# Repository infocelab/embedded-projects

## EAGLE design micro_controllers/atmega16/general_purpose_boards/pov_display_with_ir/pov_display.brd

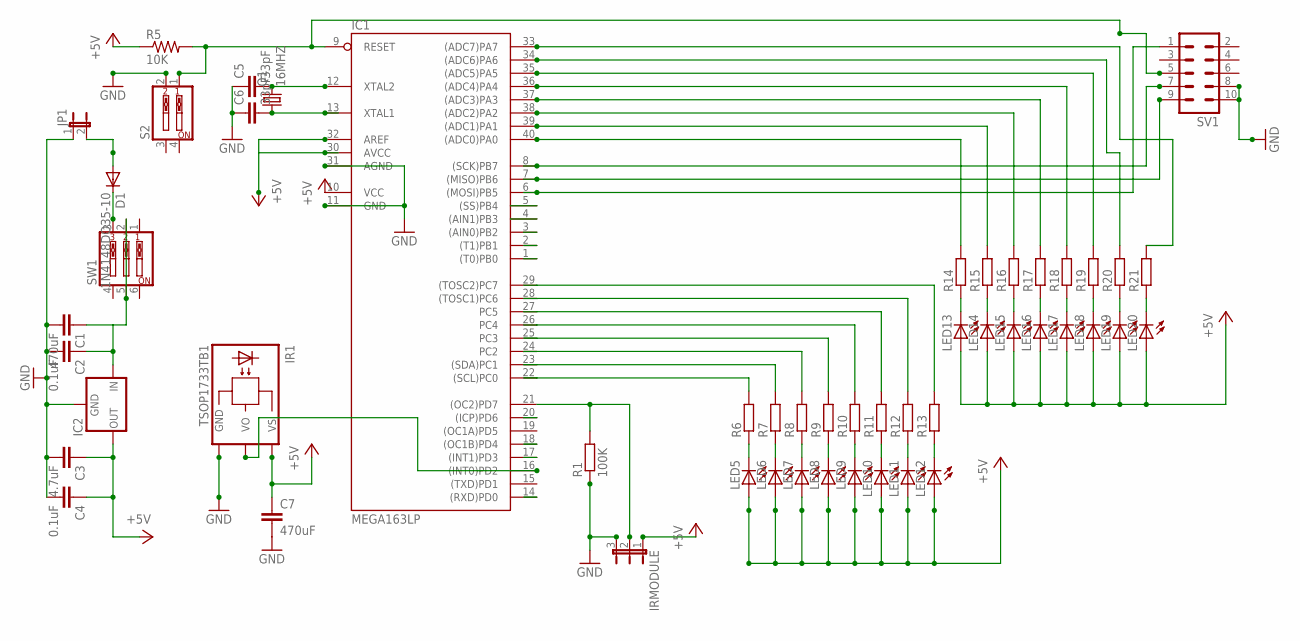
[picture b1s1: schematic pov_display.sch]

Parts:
C1, C7: 470uF; C2.5-4
C2, C4: 0.1uF; C2.5-4
C3: 4.7uF; C2.5-4
C5, C6: 33pF; C2.5-4
D1: 1N4148DO35-10; DO35-10
IC1: MEGA163LP; DIL40
IC2: 78XXS
IR1: TSOP1733TB1; TSOP17_TB1
IRMODULE: JP2W
JP1: JP1E; JP1
LED5, LED6, LED7, LED8, LED9, LED10, LED11, LED12, LED13, LED14, LED15, LED16, LED17, LED18, LED19, LED20: LED_ELD260; LED_LD260
Q1: 16MHZ; HC49U-V
R1: 100K; 0207/7
R5: 10K; 0204/7
R6, R7, R8, R9, R10, R11, R12, R13, R14, R15, R16, R17, R18, R19, R20, R21: R-EU_0207/7; 0207/7
S2: SW_DIP-2; EDG-02
SV1: MA05-2
SW1: SW_DIP-3; EDG-03

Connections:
+5V: C3.1, C4.1, C7.1, IC1.10 (VCC), IC1.30 (AVCC), IC1.32 (AREF), IC2.OUT, IR1.VS, IRMODULE.1, LED5.A, LED6.A, LED7.A, LED8.A, LED9.A, LED10.A, LED11.A, LED12.A, LED13.A, LED14.A, LED15.A, LED16.A, LED17.A, LED18.A, LED19.A, LED20.A, R5.1
GND: C1.2, C2.2, C3.2, C4.2, C5.1, C6.1, C7.2, IC1.11 (GND), IC1.31 (AGND), IC2.GND, IR1.GND, IRMODULE.3, JP1.1, R1.1, S2.2, SV1.8, SV1.10
unnamed: D1.A, JP1.2
unnamed: LED12.K (C), R13.1
unnamed: C5.2, IC1.12 (XTAL2), Q1.2
unnamed: C6.2, IC1.13 (XTAL1), Q1.1
unnamed: IC1.9 (RESET), R5.2, S2.1, SV1.5
unnamed: IC1.22 ((SCL)PC0), R6.2
unnamed: D1.C, SW1.3
unnamed: C1.1, C2.1, IC2.IN, SW1.2, SW1.5
unnamed: IC1.21 ((OC2)PD7), IRMODULE.2, R1.2
unnamed: IC1.28 ((TOSC1)PC6), R12.2
unnamed: LED10.K (C), R11.1
unnamed: IC1.26 (PC4), R10.2
unnamed: LED9.K (C), R10.1
unnamed: IC1.25 (PC3), R9.2
unnamed: LED8.K (C), R9.1
unnamed: LED7.K (C), R8.1
unnamed: IC1.6 ((MOSI)PB5), SV1.1
unnamed: IC1.7 ((MISO)PB6), SV1.9
unnamed: IC1.8 ((SCK)PB7), SV1.7
unnamed: IC1.23 ((SDA)PC1), R7.2
unnamed: IC1.33 ((ADC7)PA7), R21.2
unnamed: IC1.34 ((ADC6)PA6), R20.2
unnamed: IC1.35 ((ADC5)PA5), R19.2
unnamed: IC1.36 ((ADC4)PA4), R18.2
unnamed: IC1.37 ((ADC3)PA3), R17.2
unnamed: IC1.38 ((ADC2)PA2), R16.2
unnamed: IC1.39 ((ADC1)PA1), R15.2
unnamed: IC1.40 ((ADC0)PA0), R14.2
unnamed: IC1.24 (PC2), R8.2
unnamed: IC1.27 (PC5), R11.2
unnamed: IC1.29 ((TOSC2)PC7), R13.2
unnamed: LED6.K (C), R7.1
unnamed: LED20.K (C), R21.1
unnamed: LED19.K (C), R20.1
unnamed: LED18.K (C), R19.1
unnamed: LED17.K (C), R18.1
unnamed: LED15.K (C), R16.1
unnamed: LED13.K (C), R14.1
unnamed: LED16.K (C), R17.1
unnamed: LED14.K (C), R15.1
unnamed: LED5.K (C), R6.1
unnamed: LED11.K (C), R12.1
unnamed: IC1.16 ((INT0)PD2), IR1.VO

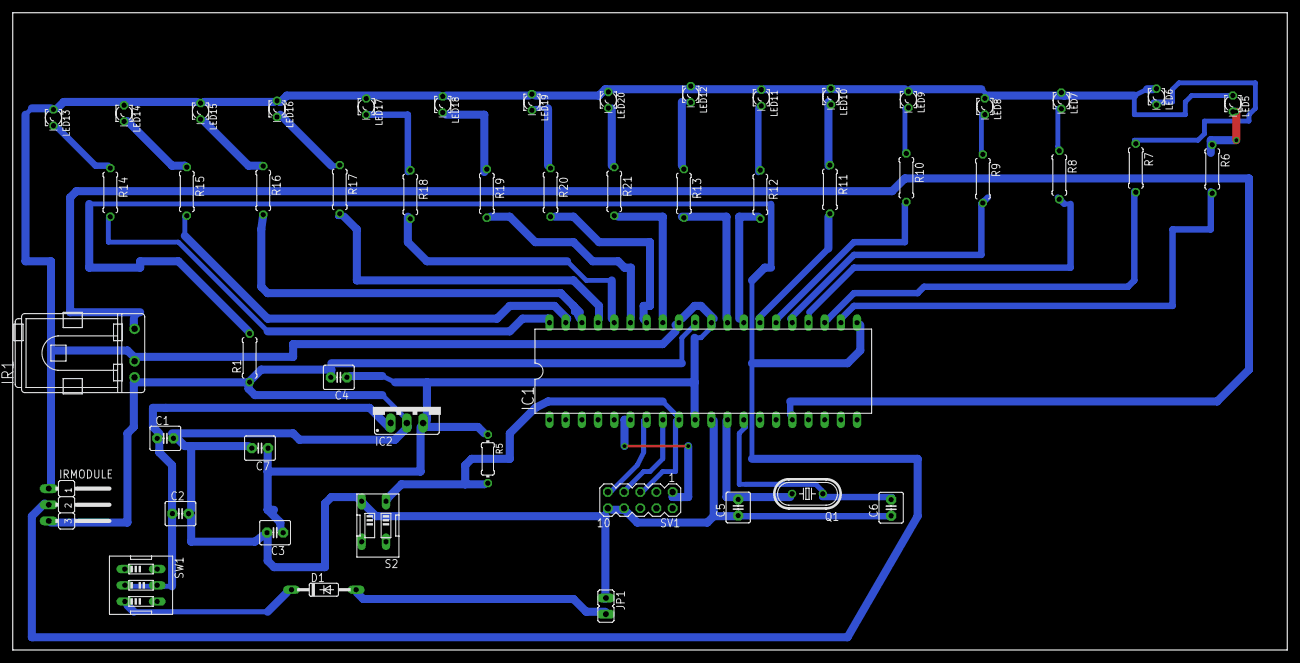
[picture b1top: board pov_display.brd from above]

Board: 2 copper layers, 200.0 x 100.0 mm, 51 parts (0 on the bottom side), 45 nets.

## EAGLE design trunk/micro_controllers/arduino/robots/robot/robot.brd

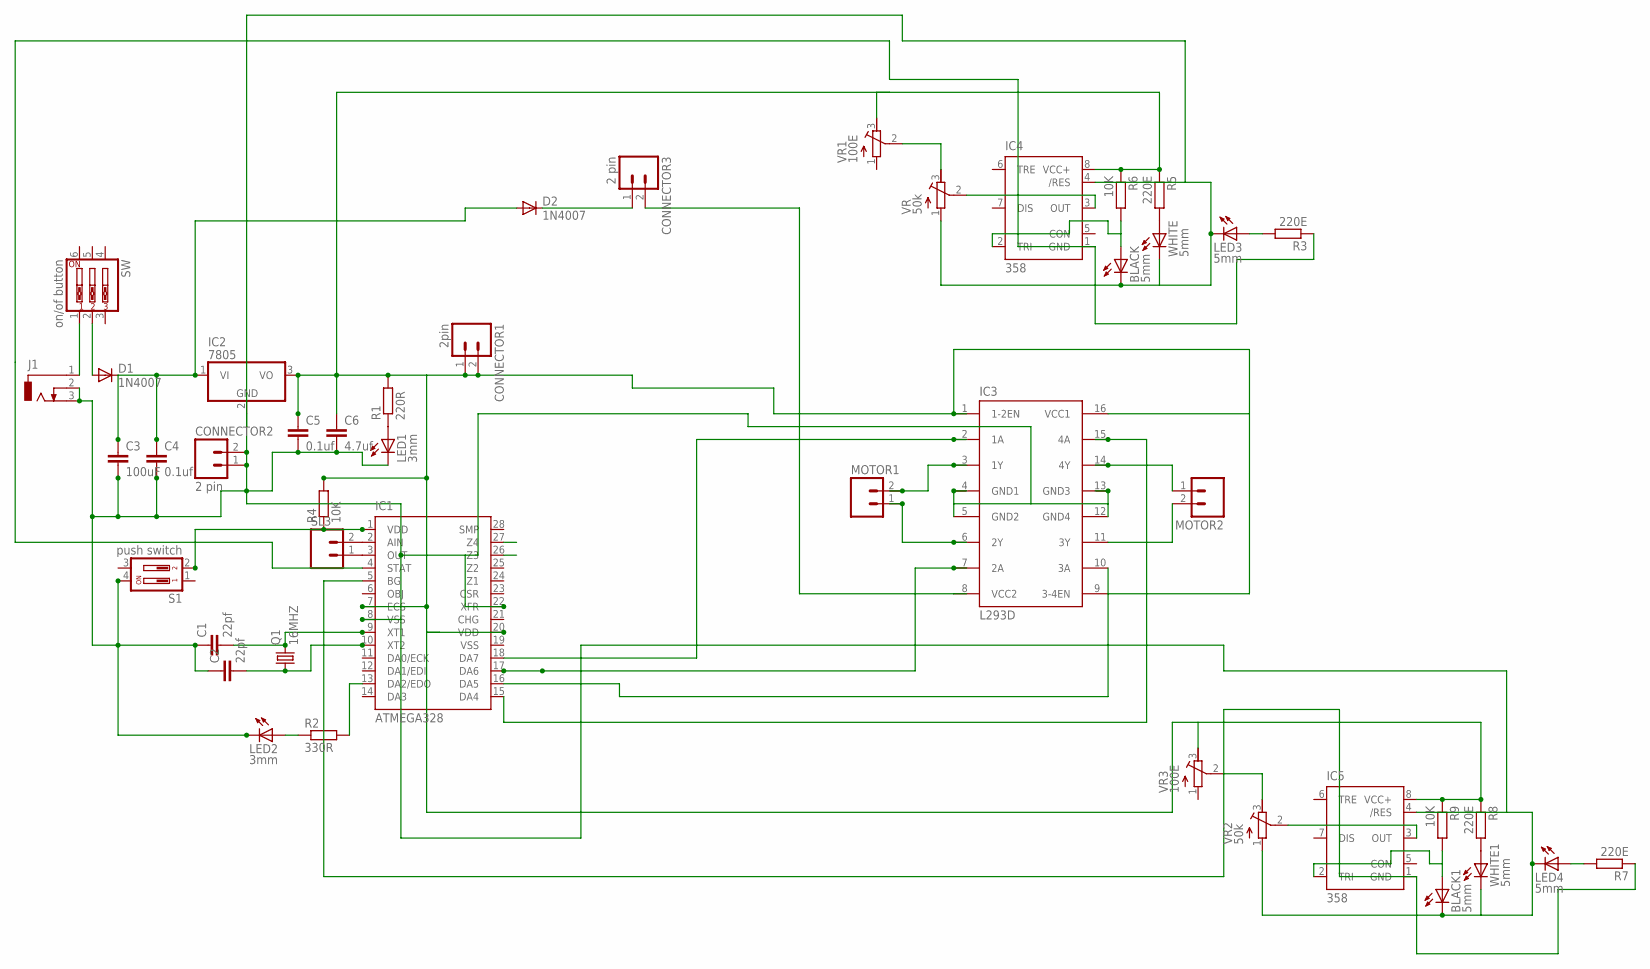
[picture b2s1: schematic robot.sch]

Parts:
BLACK, BLACK1: 5mm; LED5MM
C1, C2: 22pf; C2.5-2
C3: 100uF; C2.5-2
C4, C5: 0.1uf; C2.5-2
C6: 4.7uf; C2.5-2
CONNECTOR1: 2pin; 02P
CONNECTOR2, CONNECTOR3: 2 pin; 02P
D1, D2: 1N4007; DO41-10
IC1: ATMEGA328; DIL28-3
IC2: 7805; TO220V
IC3: L293D; DIL16
IC4, IC5: 358; DIL-08
J1: DCJ0303
LED1, LED2: 3mm; LED3MM
LED3, LED4: 5mm; LED5MM
MOTOR1, MOTOR2: M02; 02P
Q1: 16MHZ; HC49/S
R1: 220R; 0207/10
R2: 330R; 0207/10
R3, R5, R7, R8: 220E; 0204/7
R4: 10K; 0207/10
R6, R9: 10K; 0204/7
S1: push switch; DP-02
SL3: M02; 02P
SW: on/of button; EDG-03
VR, VR2: 50k; RTRIM64P
VR1, VR3: 100E; RTRIM64P
WHITE, WHITE1: 5mm; LED5MM

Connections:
unnamed: C1.2, IC1.9 (XT1), Q1.2
unnamed: C2.2, IC1.10 (XT2), Q1.1
unnamed: J1.1, SW.1
unnamed: CONNECTOR3.2, IC3.8 (VCC2)
unnamed: C3.1, C4.1, D1.C, D2.A, IC2.1 (VI)
unnamed: LED1.A, R1.1
unnamed: IC1.17 (DA6), IC3.7 (2A)
unnamed: IC1.3 (OUT), SL3.1
unnamed: IC1.2 (AIN), SL3.2
unnamed: CONNECTOR3.1, D2.C
unnamed: IC1.18 (DA7), IC3.2 (1A)
unnamed: IC1.15 (DA4), IC3.15 (4A)
unnamed: IC1.13 (DA2/EDO), R2.2
unnamed: D1.A, SW.2
unnamed: IC1.4 (STAT), IC4.1 (GND), R3.1
unnamed: IC1.16 (DA5), IC3.10 (3A)
unnamed: R5.2, WHITE.A
unnamed: BLACK.A, IC4.2 (TRI), R6.2
unnamed: IC4.3 (OUT), VR.2 (S)
unnamed: IC3.14 (4Y), MOTOR2.1
unnamed: VR.3 (A), VR1.2 (S)
unnamed: IC3.11 (3Y), MOTOR2.2
unnamed: LED3.A, R3.2
unnamed: IC1.1 (VDD), R4.1, S1.2
unnamed: LED2.A, R2.1
unnamed: C5.1, C6.1, CONNECTOR1.1, CONNECTOR1.2, IC1.7 (ECS), IC1.20 (VDD), IC2.3 (VO), IC3.1 (1-2EN), IC3.9 (3-4EN), IC3.16 (VCC1), IC4.8 (VCC+), IC5.8 (VCC+), R1.2, R4.2, R5.1, R6.1, R8.1, R9.1, VR1.3 (A), VR3.3 (A)
unnamed: IC3.6 (2Y), MOTOR1.1
unnamed: IC3.3 (1Y), MOTOR1.2
unnamed: IC1.5 (BG), IC5.1 (GND), R7.1
unnamed: R8.2, WHITE1.A
unnamed: BLACK1.A, IC5.2 (TRI), R9.2
unnamed: IC5.3 (OUT), VR2.2 (S)
unnamed: VR2.3 (A), VR3.2 (S)
unnamed: BLACK.K (C), BLACK1.K (C), C1.1, C2.1, C3.2, C4.2, C5.2, C6.2, CONNECTOR2.1, CONNECTOR2.2, IC1.8 (VSS), IC1.22 (XFR), IC2.2 (GND), IC3.4 (GND1), IC3.5 (GND2), IC3.12 (GND4), IC3.13 (GND3), IC4.4 (/RES), IC5.4 (/RES), J1.2, J1.3, LED1.K (C), LED2.K (C), LED3.K (C), LED4.K (C), S1.4, VR.1 (E), VR2.1 (E), WHITE.K (C), WHITE1.K (C)
unnamed: LED4.A, R7.2

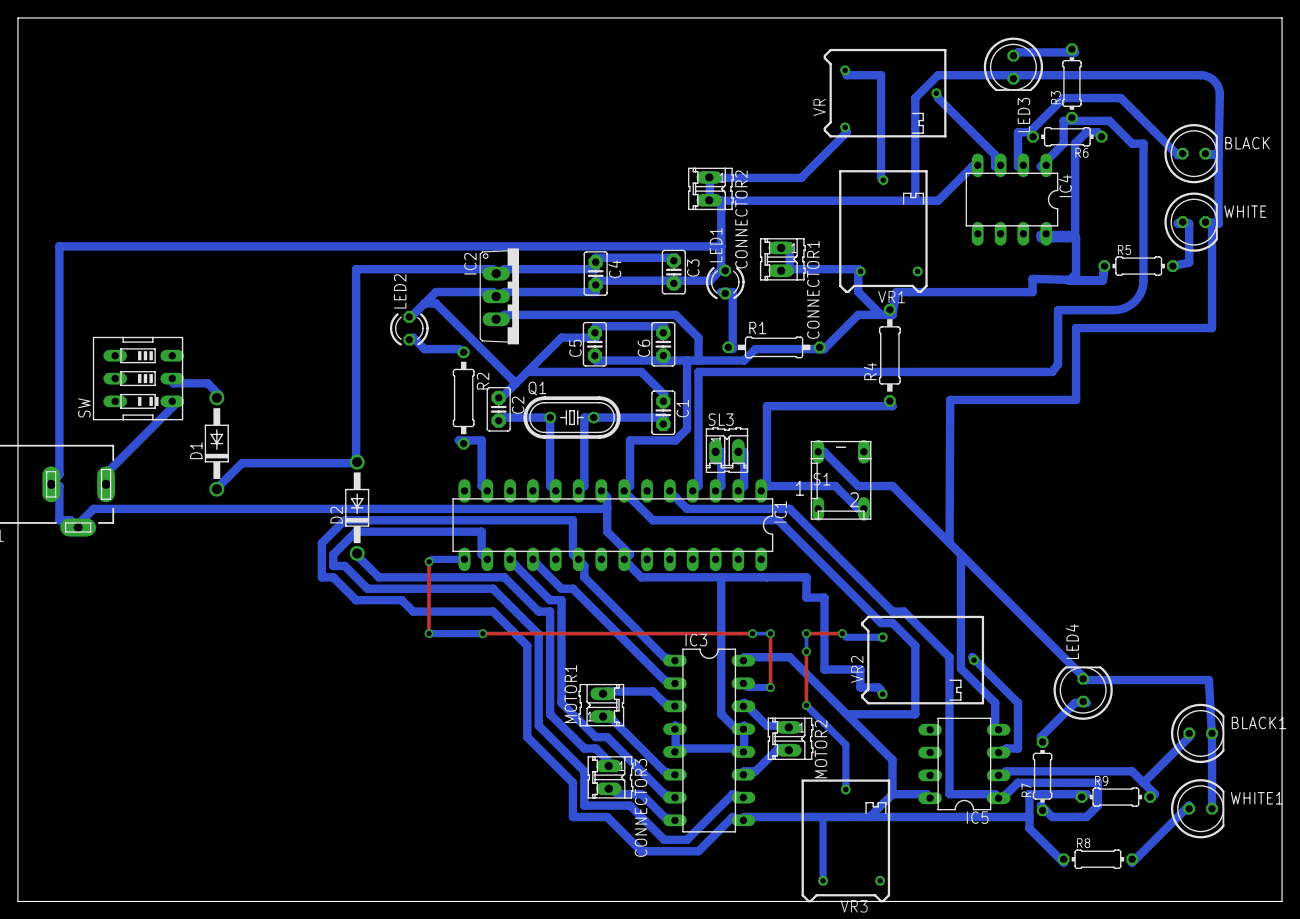
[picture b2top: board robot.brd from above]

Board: 2 copper layers, 140.7 x 98.3 mm, 44 parts (0 on the bottom side), 35 nets.

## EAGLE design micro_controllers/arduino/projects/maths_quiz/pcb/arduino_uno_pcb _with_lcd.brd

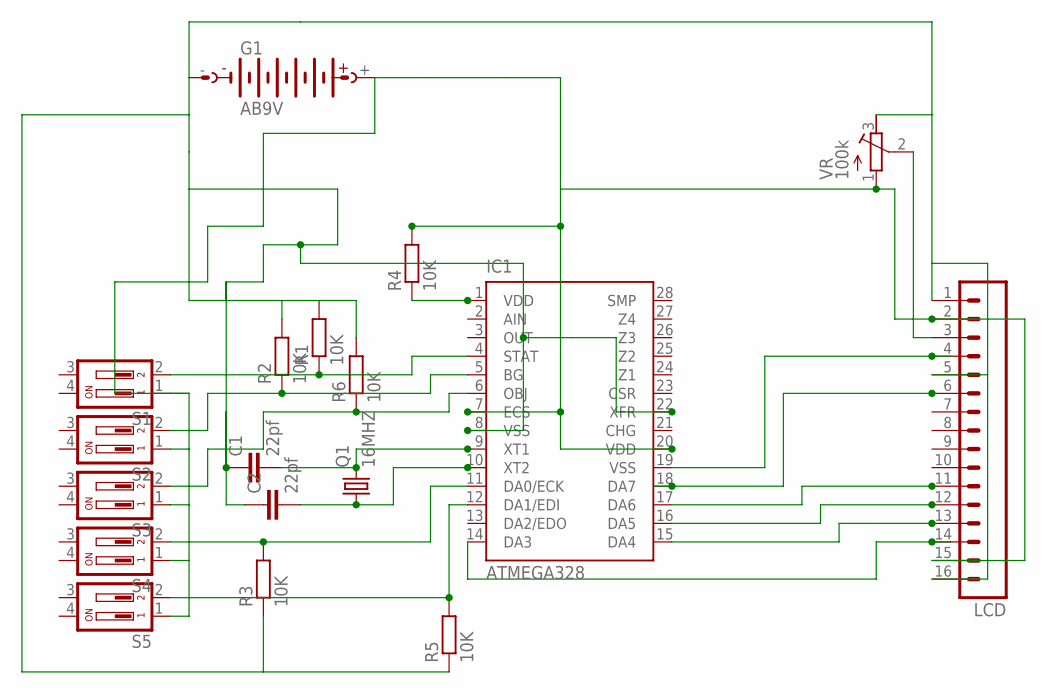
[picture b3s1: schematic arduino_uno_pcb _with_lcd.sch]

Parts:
C1, C2: 22pf; C2.5-2
G1: AB9V
IC1: ATMEGA328; DIL28-3
LCD: M16; 16P
Q1: 16MHZ; HC49/S
R1, R2, R3, R4, R5, R6: 10K; 0207/10
S1: DP02; DP-02
S2, S3, S4, S5: DP02; DP-02; MPN MCDP02
VR: 100k; RTRIM64P

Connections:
unnamed: C1.2, IC1.9 (XT1), Q1.2
unnamed: C2.2, IC1.10 (XT2), Q1.1
unnamed: G1.+, IC1.7 (ECS), IC1.20 (VDD), LCD.2, LCD.15, R4.2, S1.1, S2.1, S3.1, S4.1, S5.1, VR.1 (E)
unnamed: IC1.11 (DA0/ECK), R3.2, S4.2
unnamed: IC1.4 (STAT), R1.1, S1.2
unnamed: C1.1, C2.1, G1.-, IC1.8 (VSS), IC1.22 (XFR), LCD.1, LCD.5, LCD.16, R1.2, R2.2, R3.1, R5.1, R6.2, VR.3 (A)
unnamed: IC1.5 (BG), R2.1, S2.2
unnamed: IC1.6 (OBJ), R6.1, S3.2
unnamed: IC1.12 (DA1/EDI), R5.2, S5.2
unnamed: LCD.3, VR.2 (S)
unnamed: IC1.19 (VSS), LCD.4
unnamed: IC1.18 (DA7), LCD.6
unnamed: IC1.17 (DA6), LCD.11
unnamed: IC1.16 (DA5), LCD.12
unnamed: IC1.15 (DA4), LCD.13
unnamed: IC1.14 (DA3), LCD.14
unnamed: IC1.1 (VDD), R4.1

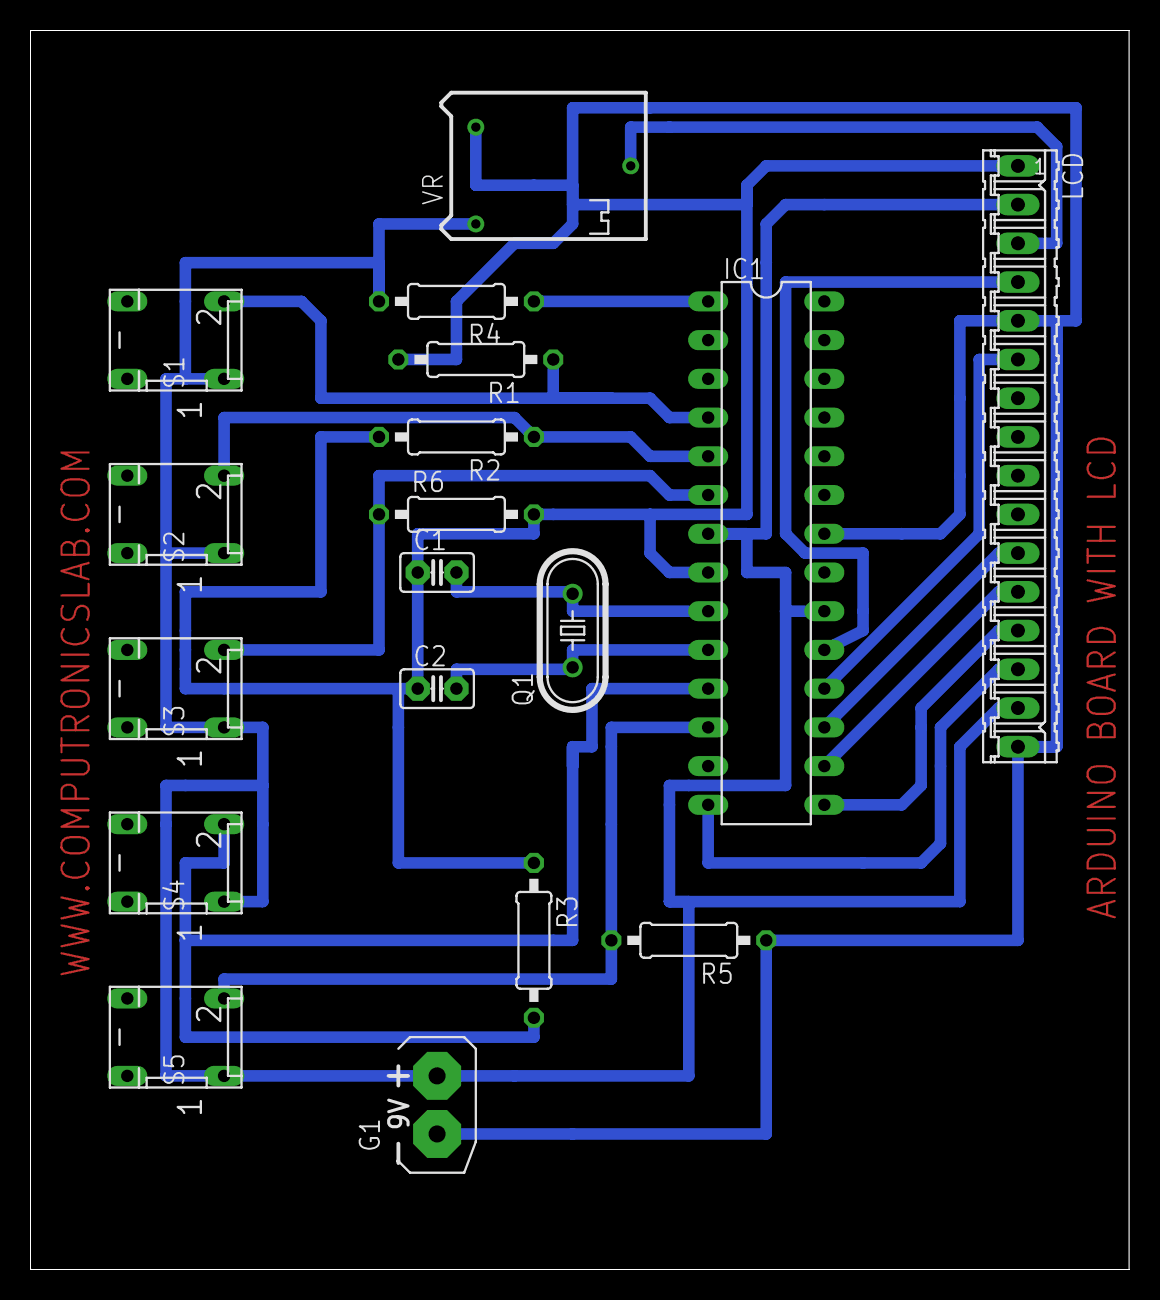
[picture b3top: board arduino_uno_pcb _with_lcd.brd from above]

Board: 2 copper layers, 72.1 x 81.3 mm, 18 parts (0 on the bottom side), 17 nets.

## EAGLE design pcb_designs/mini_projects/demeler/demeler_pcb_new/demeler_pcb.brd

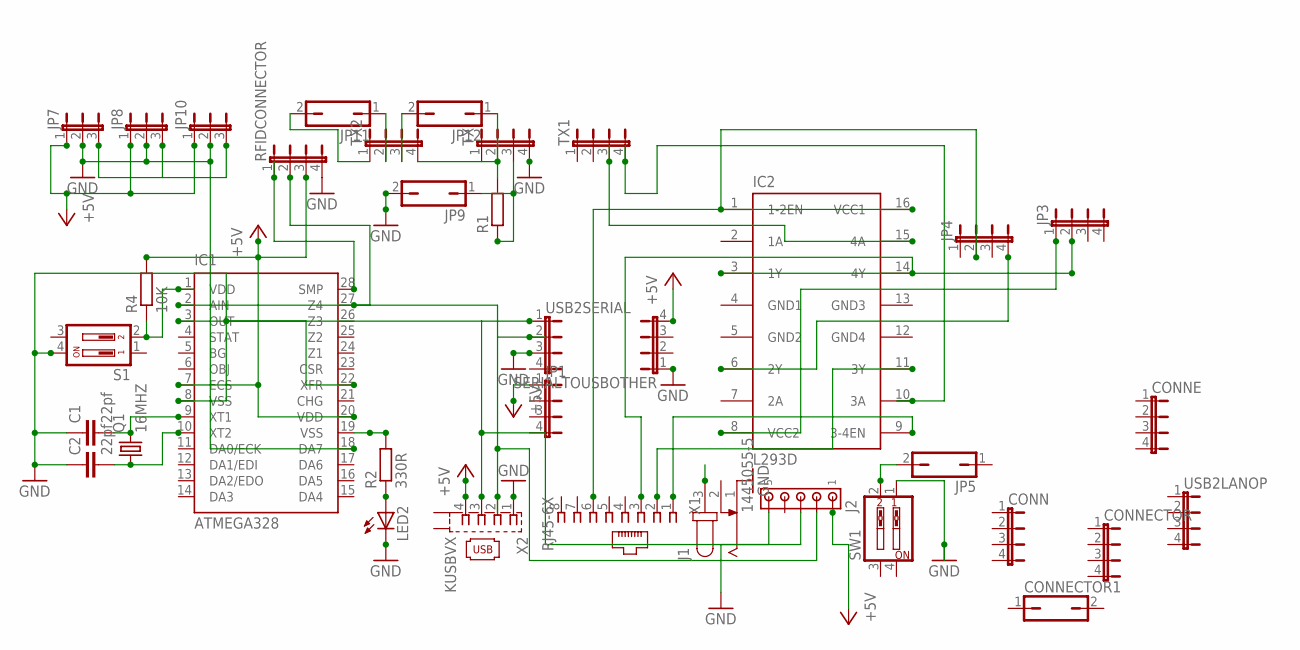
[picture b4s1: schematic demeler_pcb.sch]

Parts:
C1, C2: 22pf; C2.5-2
CONN: JP4E; JP4
CONNE: JP4E; JP4
CONNECTOR: JP4E; JP4
CONNECTOR1: JP1Q; JP1
IC1: ATMEGA328; DIL28-3
IC2: L293D; DIL16
J1: JACK-PLUG0; SPC4077
J2: 1445055-5
JP1, JP3, JP4: JP4E; JP4
JP5, JP9, JP11, JP12: JP1Q; JP1
JP7, JP8, JP10: JP2E; JP2
LED2: LED3MM
Q1: 16MHZ; HC49/S
R1: R-EU_0204/7; 0204/7
R2: 330R; 0207/10
R4: 10K; 0207/10
RFIDCONNECTOR: JP4E; JP4
S1: DP02; DP-02
SERIALTOUSBOTHER: JP4E; JP4
SW1: SW_DIP-2; EDG-02
TX, TX1, TX2: JP4E; JP4
USB2LANOP, USB2SERIAL: JP4E; JP4
X1: RJ45-6X; RJ45-NO-SHIELD
X2: KUSBVX

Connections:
+5V: IC1.7 (ECS), IC1.20 (VDD), J2.1, JP1.1, JP7.1, JP8.1, JP10.1, R4.2, RFIDCONNECTOR.3, SERIALTOUSBOTHER.4, X2.4
GND: C1.1, C2.1, IC1.8 (VSS), IC1.18 (DA7), IC1.22 (XFR), J1.1, J2.5, JP7.2, JP8.2, JP9.2, JP10.2, LED2.K (C), RFIDCONNECTOR.4, S1.4, SERIALTOUSBOTHER.1, SW1.1, TX.4, USB2SERIAL.3, X2.1
GND1: IC2.4 (GND1)
GND2: IC2.5 (GND2)
GND3: IC2.13 (GND3)
GND4: IC2.12 (GND4)
unnamed: C1.2, IC1.9 (XT1), Q1.2
unnamed: C2.2, IC1.10 (XT2), Q1.1
unnamed: IC1.3 (OUT), J2.3, USB2SERIAL.1, X2.3
unnamed: IC1.19 (VSS), R2.2
unnamed: IC2.9 (3-4EN), X1.1
unnamed: IC2.11 (3Y), X1.2
unnamed: IC2.14 (4Y), X1.3
unnamed: IC2.16 (VCC1), X1.6
unnamed: IC2.8 (VCC2), JP3.1
unnamed: IC2.6 (2Y), JP4.4
unnamed: IC2.3 (1Y), JP3.2
unnamed: IC2.1 (1-2EN), JP4.2
unnamed: IC2.10 (3A), TX1.4
unnamed: IC2.15 (4A), TX1.3
unnamed: R1.2, TX.2
unnamed: JP9.1, R1.1, TX.3
unnamed: IC1.2 (AIN), J2.2, USB2SERIAL.2, X2.2
unnamed: JP5.2, SW1.2
unnamed: IC1.27 (Z4), RFIDCONNECTOR.2
unnamed: IC1.28 (SMP), RFIDCONNECTOR.1
unnamed: JP7.3, JP8.3, JP10.3
unnamed: JP11.2, TX2.1
unnamed: JP11.1, TX2.2
unnamed: JP12.2, TX2.3
unnamed: JP12.1, TX2.4
unnamed: IC1.1 (VDD), R4.1, S1.2
unnamed: LED2.A, R2.1

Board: 2 copper layers, 36 parts (0 on the bottom side), 29 nets, no tracks yet.

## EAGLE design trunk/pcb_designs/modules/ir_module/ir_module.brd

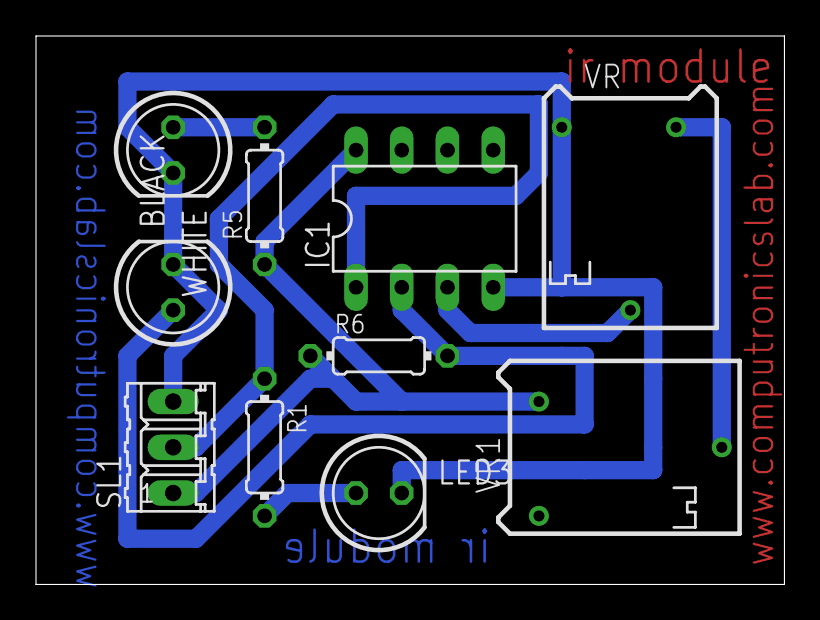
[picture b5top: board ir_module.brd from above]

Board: 2 copper layers, 41.6 x 30.5 mm, 10 parts (0 on the bottom side), 8 nets.

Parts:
BLACK: 5mm; LED5MM
IC1: 358; DIL-08
LED3: 5mm; LED5MM
R1, R5: 220E; 0204/7
R6: 10K; 0204/7
SL1: 03P
VR: 50k; RTRIM64P
VR1: 100E; RTRIM64P
WHITE: 5mm; LED5MM

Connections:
unnamed: IC1.8, R5.1, R6.1, SL1.1, VR1.3
unnamed: IC1.1, R1.1, SL1.2
unnamed: LED3.A, R1.2
unnamed: R5.2, WHITE.A
unnamed: IC1.3, VR.2
unnamed: BLACK.A, IC1.2, R6.2
unnamed: VR.3, VR1.2
unnamed: BLACK.K, IC1.4, LED3.K, SL1.3, VR.1, WHITE.K

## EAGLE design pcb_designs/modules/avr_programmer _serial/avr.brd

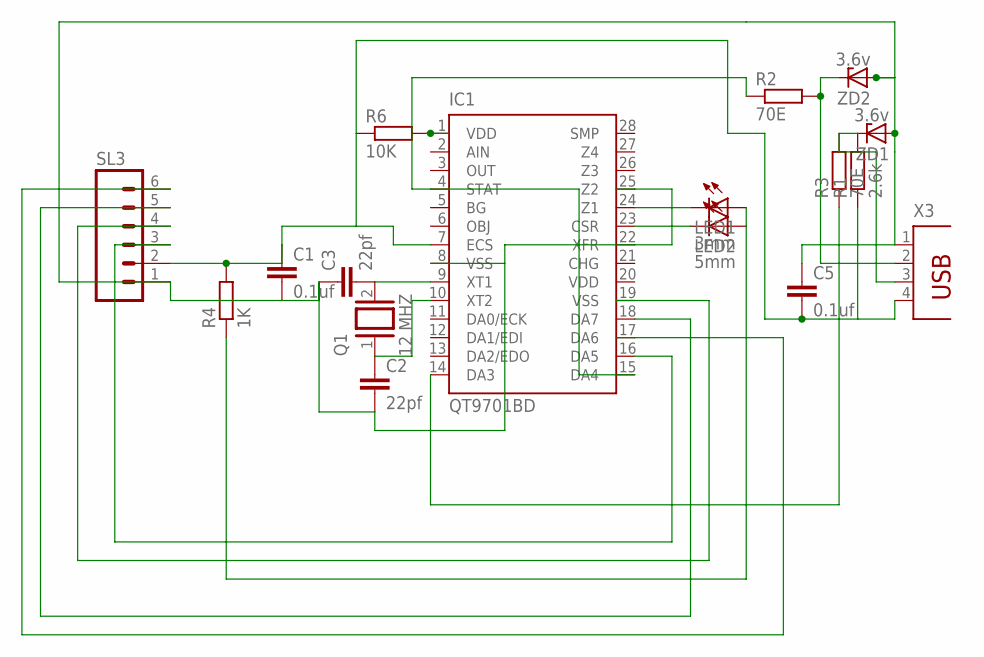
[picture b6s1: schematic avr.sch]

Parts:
C1, C5: 0.1uf; C2.5-3
C2, C3: 22pf; C2.5-3
IC1: QT9701BD; DIL28-3
LED1: 3mm; LED3MM
LED2: 5mm; LED3MM
Q1: 12 MHZ; QS
R1: 2.6k; 0204/7
R2, R3: 70E; 0204/7
R4: 1K; 0204/7
R6: 10K; 0204/7
SL3: M06; 06P
X3: PN87520
ZD1, ZD2: 3.6v; SOD81

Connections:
unnamed: C3.2, IC1.9 (XT1), Q1.2
unnamed: C2.1, IC1.10 (XT2), Q1.1
unnamed: C1.2, C2.2, C3.1, C5.1, IC1.8 (VSS), IC1.22 (XFR), IC1.25 (Z2), SL3.1, X3.1, ZD1.A, ZD2.A
unnamed: IC1.24 (Z1), LED1.K (C)
unnamed: IC1.23 (CSR), LED2.K (C)
unnamed: R2.2, X3.2, ZD2.C
unnamed: IC1.4 (STAT), IC1.15 (DA4), R2.1
unnamed: R1.2, R3.2, X3.3, ZD1.C
unnamed: LED1.A, LED2.A, R4.1
unnamed: IC1.14 (DA3), R3.1
unnamed: IC1.1 (VDD), R6.2
unnamed: IC1.17 (DA6), SL3.6
unnamed: IC1.16 (DA5), SL3.3
unnamed: IC1.18 (DA7), SL3.5
unnamed: C1.1, C5.2, IC1.7 (ECS), R1.1, R4.2, R6.1, SL3.2, X3.4
unnamed: IC1.19 (VSS), SL3.4

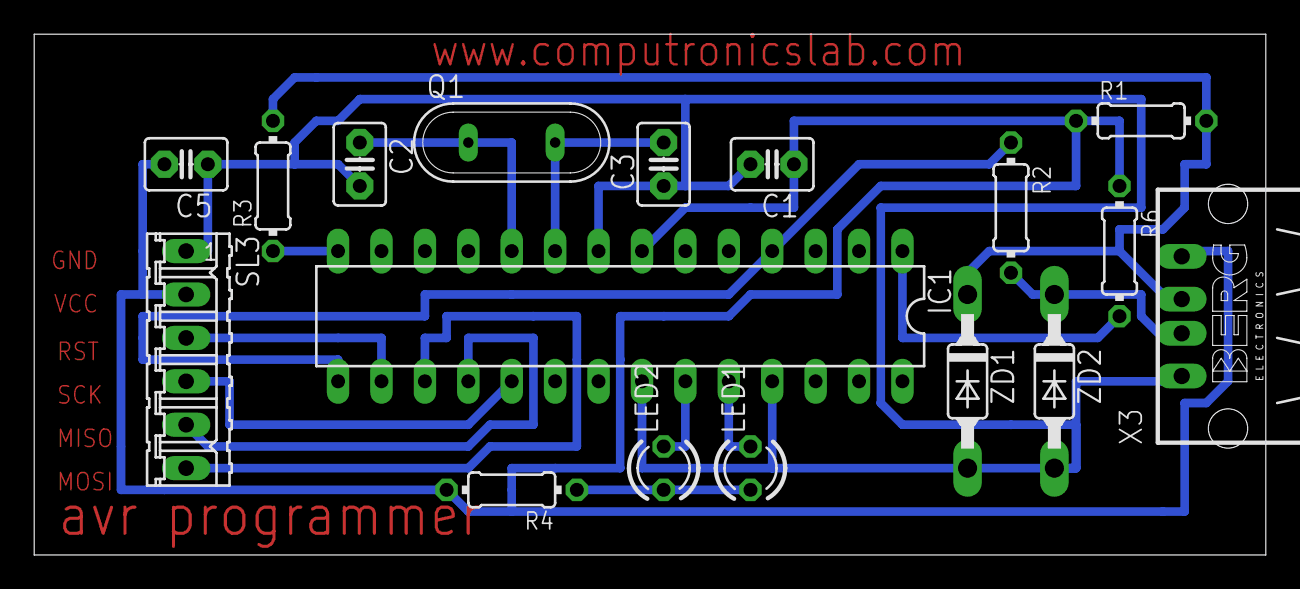
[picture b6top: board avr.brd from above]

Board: 2 copper layers, 72.1 x 30.5 mm, 17 parts (0 on the bottom side), 16 nets.

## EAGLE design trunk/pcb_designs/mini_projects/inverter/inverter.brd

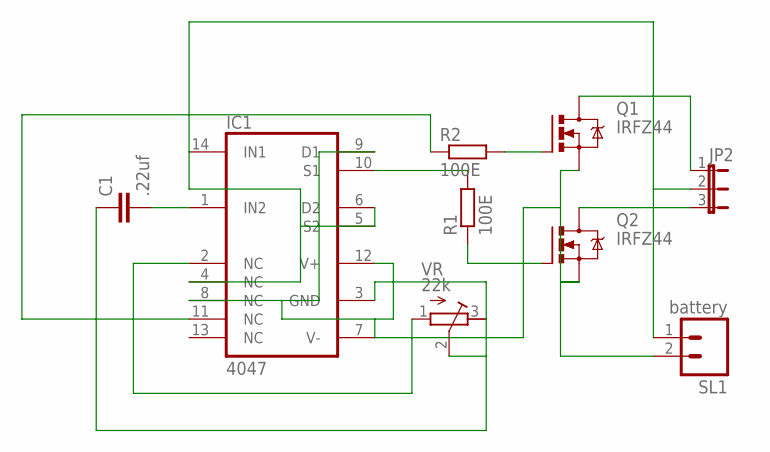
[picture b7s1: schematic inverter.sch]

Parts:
C1: .22uf; C5B3.5
IC1: 4047; DIL14
JP2: JP2E; JP2
Q1, Q2: IRFZ44; TO220BH
R1, R2: 100E; 0207/15
SL1: battery; 02P
VR: 22k; RTRIM64P

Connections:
unnamed: IC1.11 (NC), R2.1
unnamed: Q2.G, R1.1
unnamed: IC1.10 (S1), R1.2
unnamed: Q1.G, R2.2
unnamed: IC1.7 (V-), IC1.8 (NC), IC1.9 (D1), IC1.12 (V+), Q1.S, Q2.S, SL1.2
unnamed: JP2.1, Q1.D
unnamed: JP2.3, Q2.D
unnamed: IC1.4 (NC), IC1.5 (S2), IC1.6 (D2), IC1.14 (IN1), JP2.2, SL1.1
unnamed: C1.2, IC1.1 (IN2)
unnamed: IC1.2 (NC), VR.1 (E)
unnamed: C1.1, IC1.3 (GND), VR.2 (S), VR.3 (A)

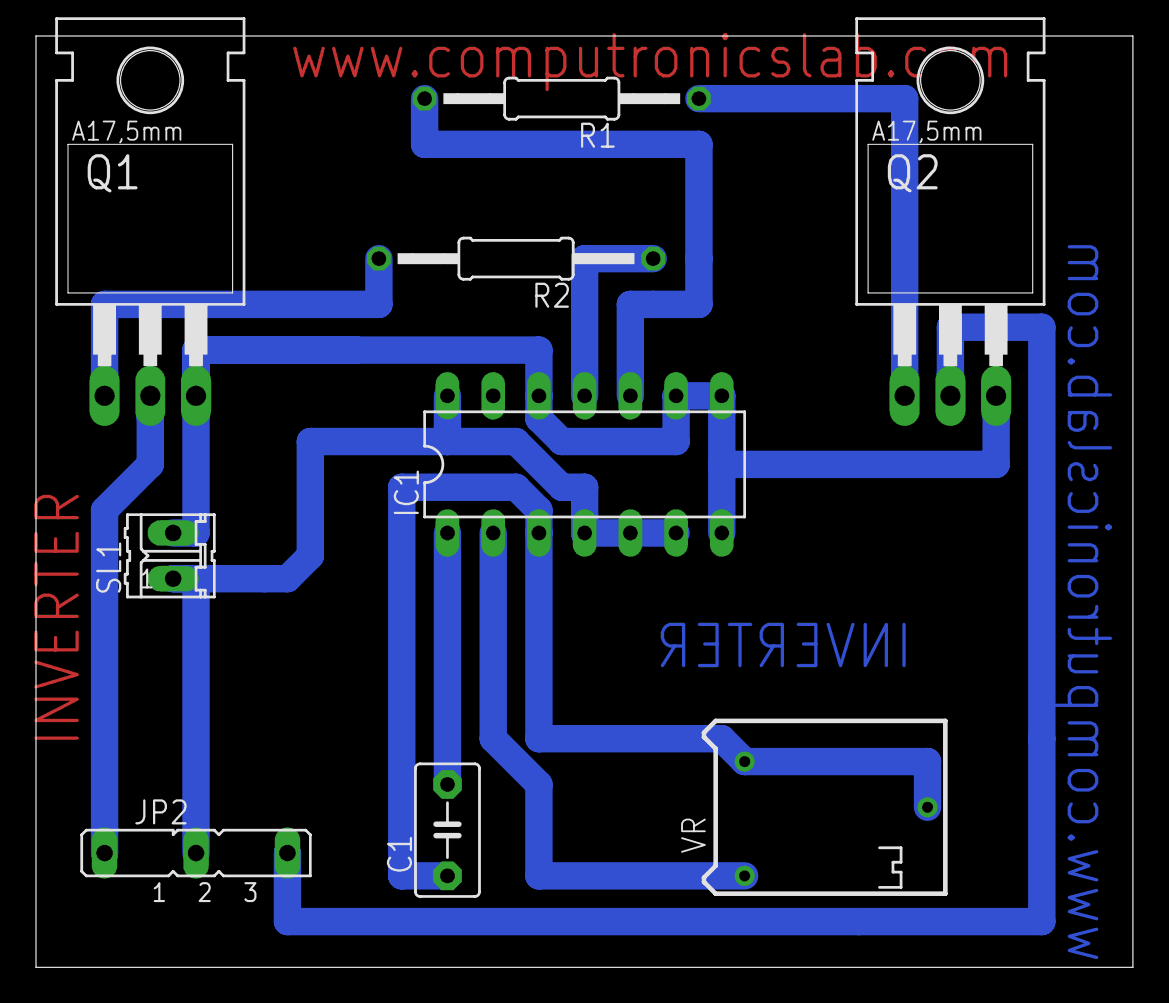
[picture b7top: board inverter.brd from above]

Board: 2 copper layers, 60.9 x 51.7 mm, 9 parts (0 on the bottom side), 11 nets.

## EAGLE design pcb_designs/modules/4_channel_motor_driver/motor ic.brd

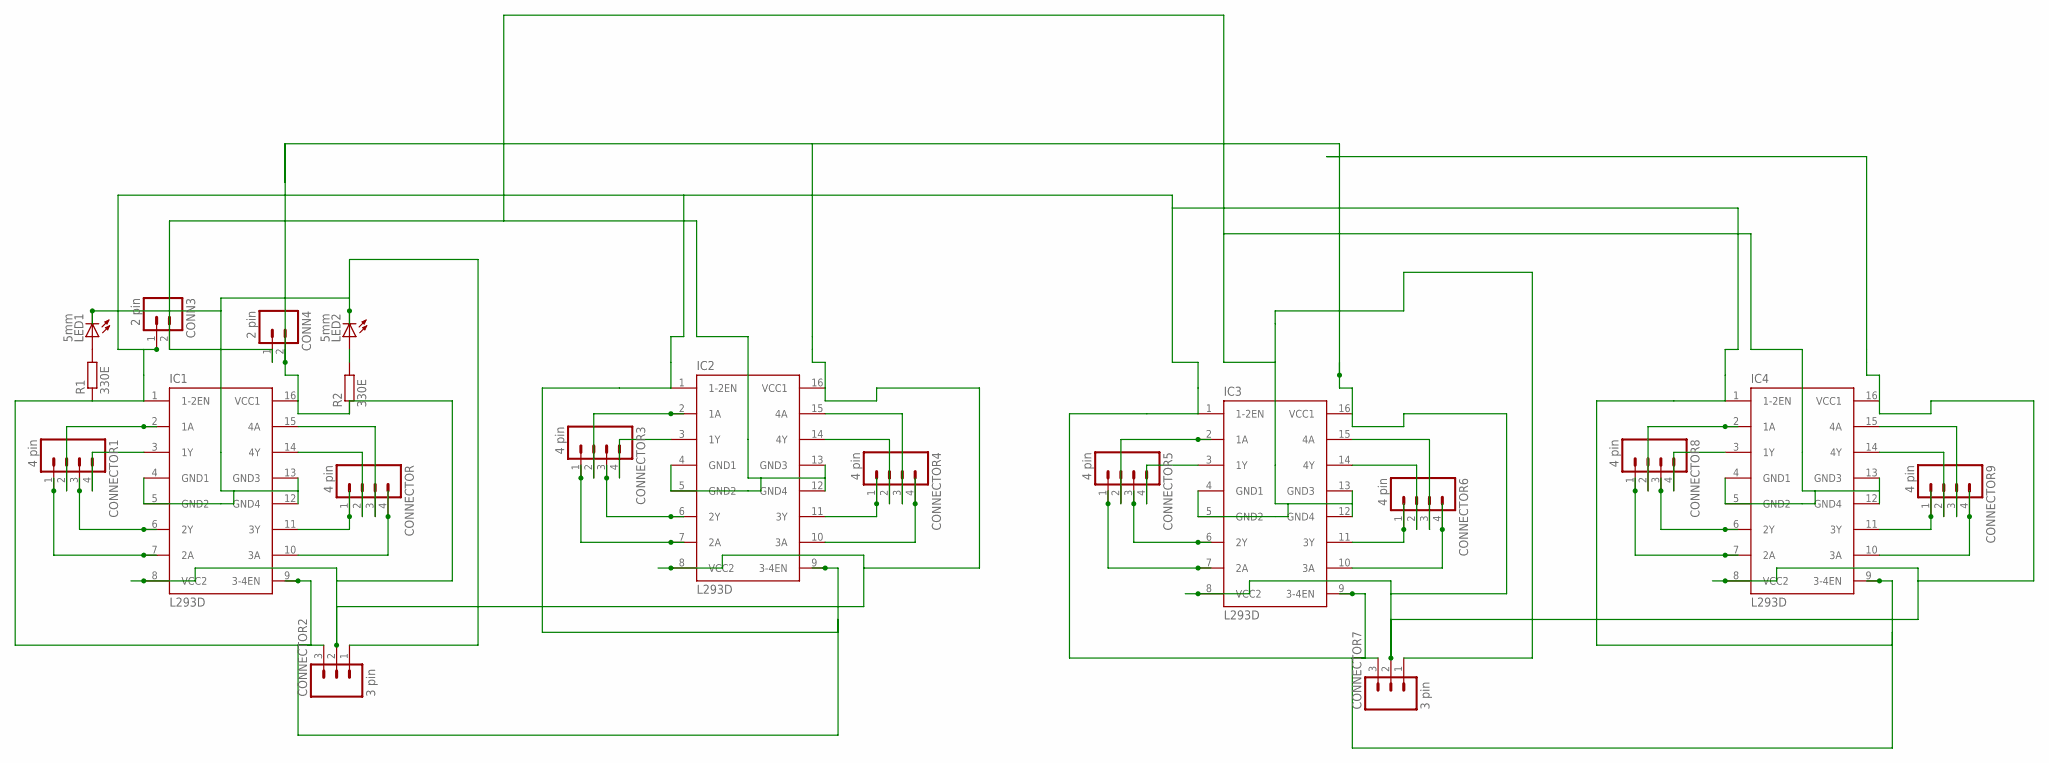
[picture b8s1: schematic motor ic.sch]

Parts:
CONN3, CONN4: 2 pin; 02P
CONNECTOR, CONNECTOR1, CONNECTOR3, CONNECTOR4, CONNECTOR5, CONNECTOR6, CONNECTOR8, CONNECTOR9: 4 pin; 04P
CONNECTOR2, CONNECTOR7: 3 pin; 03P
IC1, IC2, IC3, IC4: L293D; DIL16
LED1, LED2: 5mm; LED_LD260
R1, R2: 330E; 0204/7

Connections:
unnamed: LED1.A, R1.2
unnamed: LED2.A, R2.2
unnamed: CONNECTOR1.2, IC1.2 (1A)
unnamed: CONNECTOR1.4, IC1.3 (1Y)
unnamed: CONNECTOR1.3, IC1.6 (2Y)
unnamed: CONNECTOR1.1, IC1.7 (2A)
unnamed: CONNECTOR.3, IC1.15 (4A)
unnamed: CONNECTOR.4, IC1.10 (3A)
unnamed: CONNECTOR.2, IC1.14 (4Y)
unnamed: CONNECTOR.1, IC1.11 (3Y)
unnamed: CONN3.2, CONN4.1, CONNECTOR2.1, CONNECTOR7.1, IC1.4 (GND1), IC1.5 (GND2), IC1.12 (GND4), IC1.13 (GND3), IC2.4 (GND1), IC2.5 (GND2), IC2.12 (GND4), IC2.13 (GND3), IC3.4 (GND1), IC3.5 (GND2), IC3.12 (GND4), IC3.13 (GND3), IC4.4 (GND1), IC4.5 (GND2), IC4.12 (GND4), IC4.13 (GND3), LED1.K (C), LED2.K (C)
unnamed: CONN3.1, CONNECTOR2.3, CONNECTOR7.3, IC1.1 (1-2EN), IC1.9 (3-4EN), IC2.1 (1-2EN), IC2.9 (3-4EN), IC3.1 (1-2EN), IC3.9 (3-4EN), IC4.1 (1-2EN), IC4.9 (3-4EN), R1.1
unnamed: CONN4.2, CONNECTOR2.2, CONNECTOR7.2, IC1.8 (VCC2), IC1.16 (VCC1), IC2.8 (VCC2), IC2.16 (VCC1), IC3.8 (VCC2), IC3.16 (VCC1), IC4.8 (VCC2), IC4.16 (VCC1), R2.1
unnamed: CONNECTOR3.2, IC2.2 (1A)
unnamed: CONNECTOR3.4, IC2.3 (1Y)
unnamed: CONNECTOR3.3, IC2.6 (2Y)
unnamed: CONNECTOR3.1, IC2.7 (2A)
unnamed: CONNECTOR4.3, IC2.15 (4A)
unnamed: CONNECTOR4.4, IC2.10 (3A)
unnamed: CONNECTOR4.2, IC2.14 (4Y)
unnamed: CONNECTOR4.1, IC2.11 (3Y)
unnamed: CONNECTOR5.2, IC3.2 (1A)
unnamed: CONNECTOR5.4, IC3.3 (1Y)
unnamed: CONNECTOR5.3, IC3.6 (2Y)
unnamed: CONNECTOR5.1, IC3.7 (2A)
unnamed: CONNECTOR6.3, IC3.15 (4A)
unnamed: CONNECTOR6.4, IC3.10 (3A)
unnamed: CONNECTOR6.2, IC3.14 (4Y)
unnamed: CONNECTOR6.1, IC3.11 (3Y)
unnamed: CONNECTOR8.2, IC4.2 (1A)
unnamed: CONNECTOR8.4, IC4.3 (1Y)
unnamed: CONNECTOR8.3, IC4.6 (2Y)
unnamed: CONNECTOR8.1, IC4.7 (2A)
unnamed: CONNECTOR9.3, IC4.15 (4A)
unnamed: CONNECTOR9.4, IC4.10 (3A)
unnamed: CONNECTOR9.2, IC4.14 (4Y)
unnamed: CONNECTOR9.1, IC4.11 (3Y)

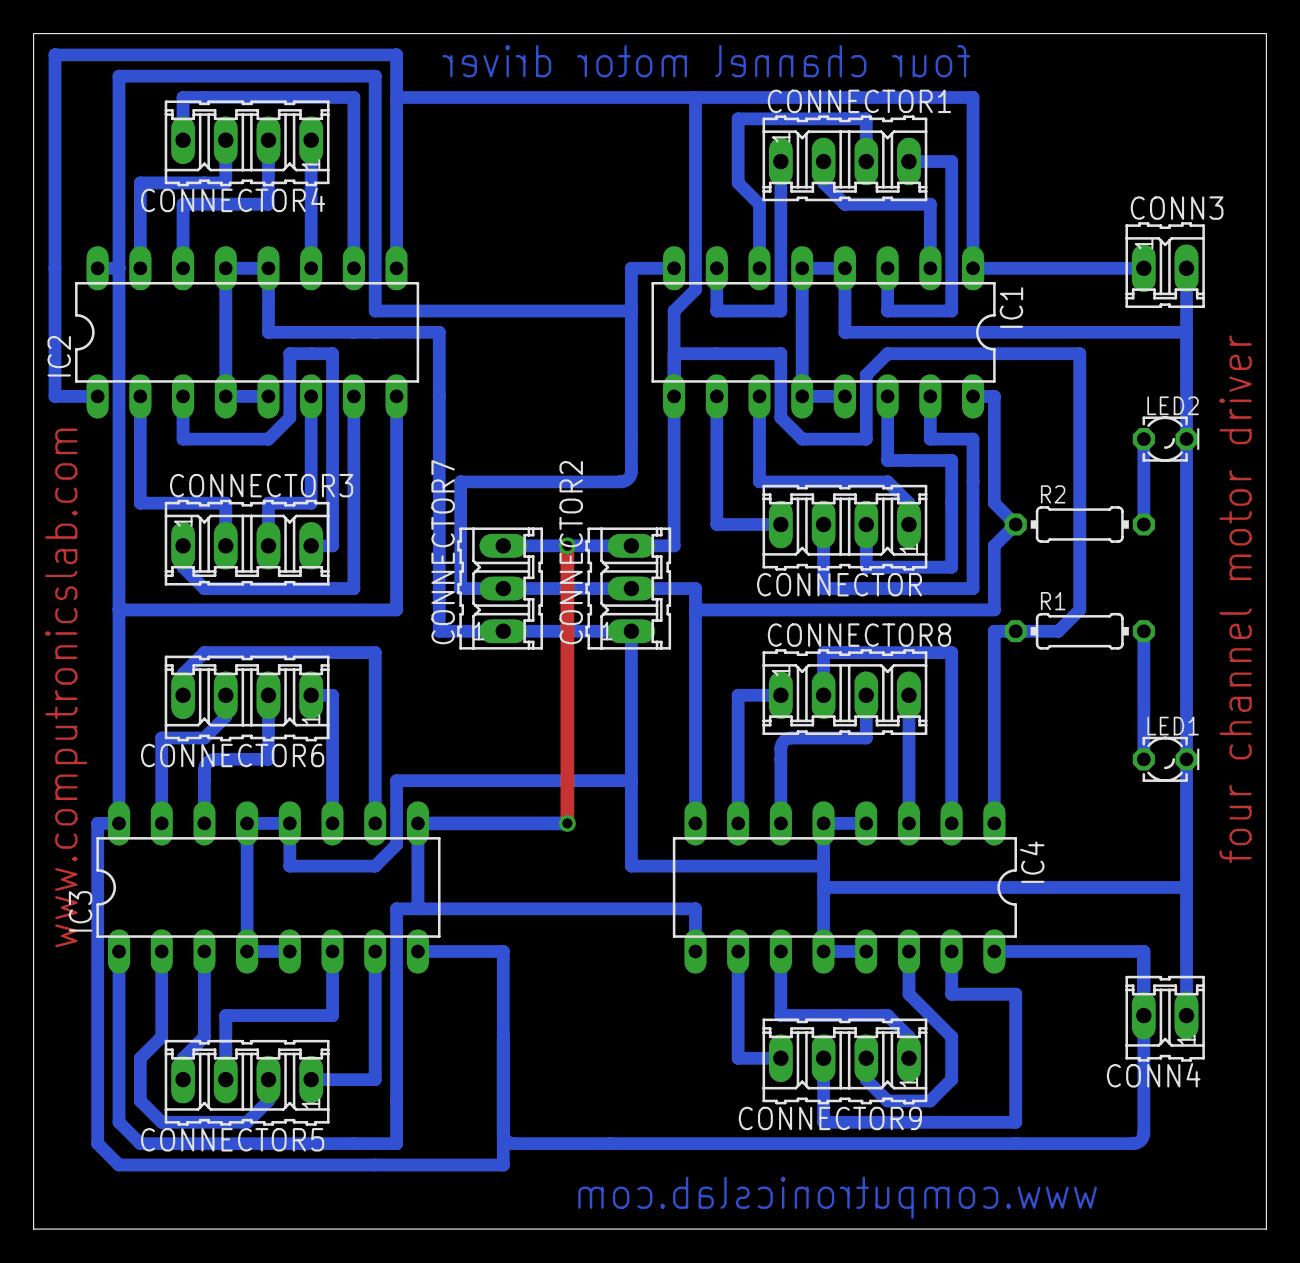
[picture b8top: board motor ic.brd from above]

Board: 2 copper layers, 73.3 x 71.1 mm, 20 parts (0 on the bottom side), 37 nets.

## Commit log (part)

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2015-07-01 success
